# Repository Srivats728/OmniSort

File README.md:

# OmniSort

**The ultimate download and email manager.**

Have you ever just stared at your download folder or your email inbox in pure horror, looking at cluttered files and unread emails you didn't even know existed? Enter OmniSort, an all-in-one physical tool to quickly and easily sort your email inbox or download folder with absolute ease. Featuring an OLED display, 16 customizable switches, and a glorious rotary knob, tactility and ease of use you get with this product is unmatched. Follow along my journey of building this and bringing it to life! Thanks for reading.

*Built by Srivats Viswanathan*

---

## Build Log
*(CAD renders, schematics, and PCB layouts will be here once they are finished).*

## Hardware
* **Microcontroller:** Seeed XIAO RP2040 
* **Inputs:** 16x MX-Style Switches & 1x EC11 Rotary Encoder
* **Display:** 0.91-inch OLED 
* **Lighting:** 16x 1N4148 Diodes (for 4x4 matrix) & 16x SK6812 MINI-E RGB LEDs
* **Case:** 3D printed enclosure secured with M3 screws and heatset inserts

## How It Works
1. **Board:** Will use KMK to handle switch matrix, track dial, and update OLED screen. 
2. **Host:** A background Python script on PC will watch local folders and talking to email servers to route data whenever a switch is hit.

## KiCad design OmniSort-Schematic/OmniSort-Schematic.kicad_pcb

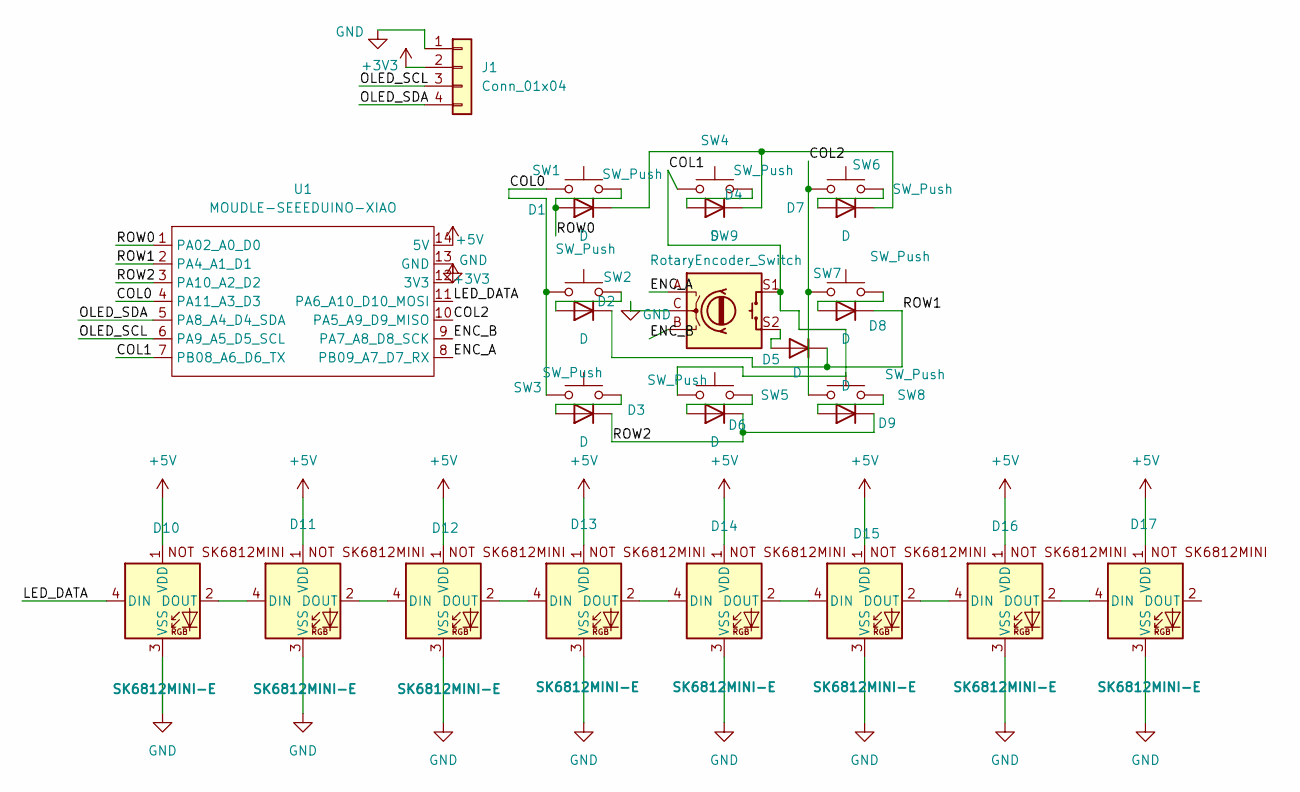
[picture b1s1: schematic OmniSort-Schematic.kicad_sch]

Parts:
D1, D2, D3, D4, D5, D6, D7, D8, D9: D; D_DO-35_SOD27_P7.62mm_Horizontal
D10, D11, D12, D13, D14, D15, D16, D17: SK6812MINI-E; SK6812MINI-E_fixed
J1: Conn_01x04; PinHeader_1x04_P2.54mm_Vertical
SW1, SW2, SW3, SW4, SW5, SW6, SW7, SW8: SW_Push; SW_Cherry_MX_1.00u_PCB
SW9: RotaryEncoder_Switch; RotaryEncoder_Alps_EC11E-Switch_Vertical_H20mm_MountingHoles
U1: MOUDLE-SEEEDUINO-XIAO; XIAO-Generic-Hybrid-14P-2.54-21X17.8MM

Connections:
+3V3: J1.2, U1.12 (3V3)
+5V: D10.1 (VDD), D11.1 (VDD), D12.1 (VDD), D13.1 (VDD), D14.1 (VDD), D15.1 (VDD), D16.1 (VDD), D17.1 (VDD), U1.14 (5V)
/COL0: SW1.1, SW2.1, SW3.1, U1.4 (PA11_A3_D3)
/COL1: SW4.1, SW5.1, SW9.S1, U1.7 (PB08_A6_D6_TX)
/COL2: SW6.1, SW7.1, SW8.1, U1.10 (PA5_A9_D9_MISO)
/ENC_A: SW9.A, U1.8 (PB09_A7_D7_RX)
/ENC_B: SW9.B, U1.9 (PA7_A8_D8_SCK)
/LED_DATA: D10.4 (DIN), U1.11 (PA6_A10_D10_MOSI)
/OLED_SCL: J1.3, U1.6 (PA9_A5_D5_SCL)
/OLED_SDA: J1.4, U1.5 (PA8_A4_D4_SDA)
/ROW0: D1.2 (A), SW1.2, U1.1 (PA02_A0_D0)
/ROW1: D2.1 (K), D5.1 (K), D8.1 (K), U1.2 (PA4_A1_D1)
/ROW2: D3.1 (K), D6.1 (K), D9.1 (K), U1.3 (PA10_A2_D2)
GND: D10.3 (VSS), D11.3 (VSS), D12.3 (VSS), D13.3 (VSS), D14.3 (VSS), D15.3 (VSS), D16.3 (VSS), D17.3 (VSS), J1.1, SW9.C, U1.13 (GND)
unnamed: D1.1 (K), D4.1 (K), D7.1 (K)
unnamed: D2.2 (A), SW2.2
unnamed: D3.2 (A), SW3.2
unnamed: D4.2 (A), SW4.2
unnamed: D5.2 (A), SW9.S2
unnamed: D6.2 (A), SW5.2
unnamed: D7.2 (A), SW6.2
unnamed: D8.2 (A), SW7.2
unnamed: D9.2 (A), SW8.2
unnamed: D10.2 (DOUT), D11.4 (DIN)
unnamed: D11.2 (DOUT), D12.4 (DIN)
unnamed: D12.2 (DOUT), D13.4 (DIN)
unnamed: D13.2 (DOUT), D14.4 (DIN)
unnamed: D14.2 (DOUT), D15.4 (DIN)
unnamed: D15.2 (DOUT), D16.4 (DIN)
unnamed: D16.2 (DOUT), D17.4 (DIN)

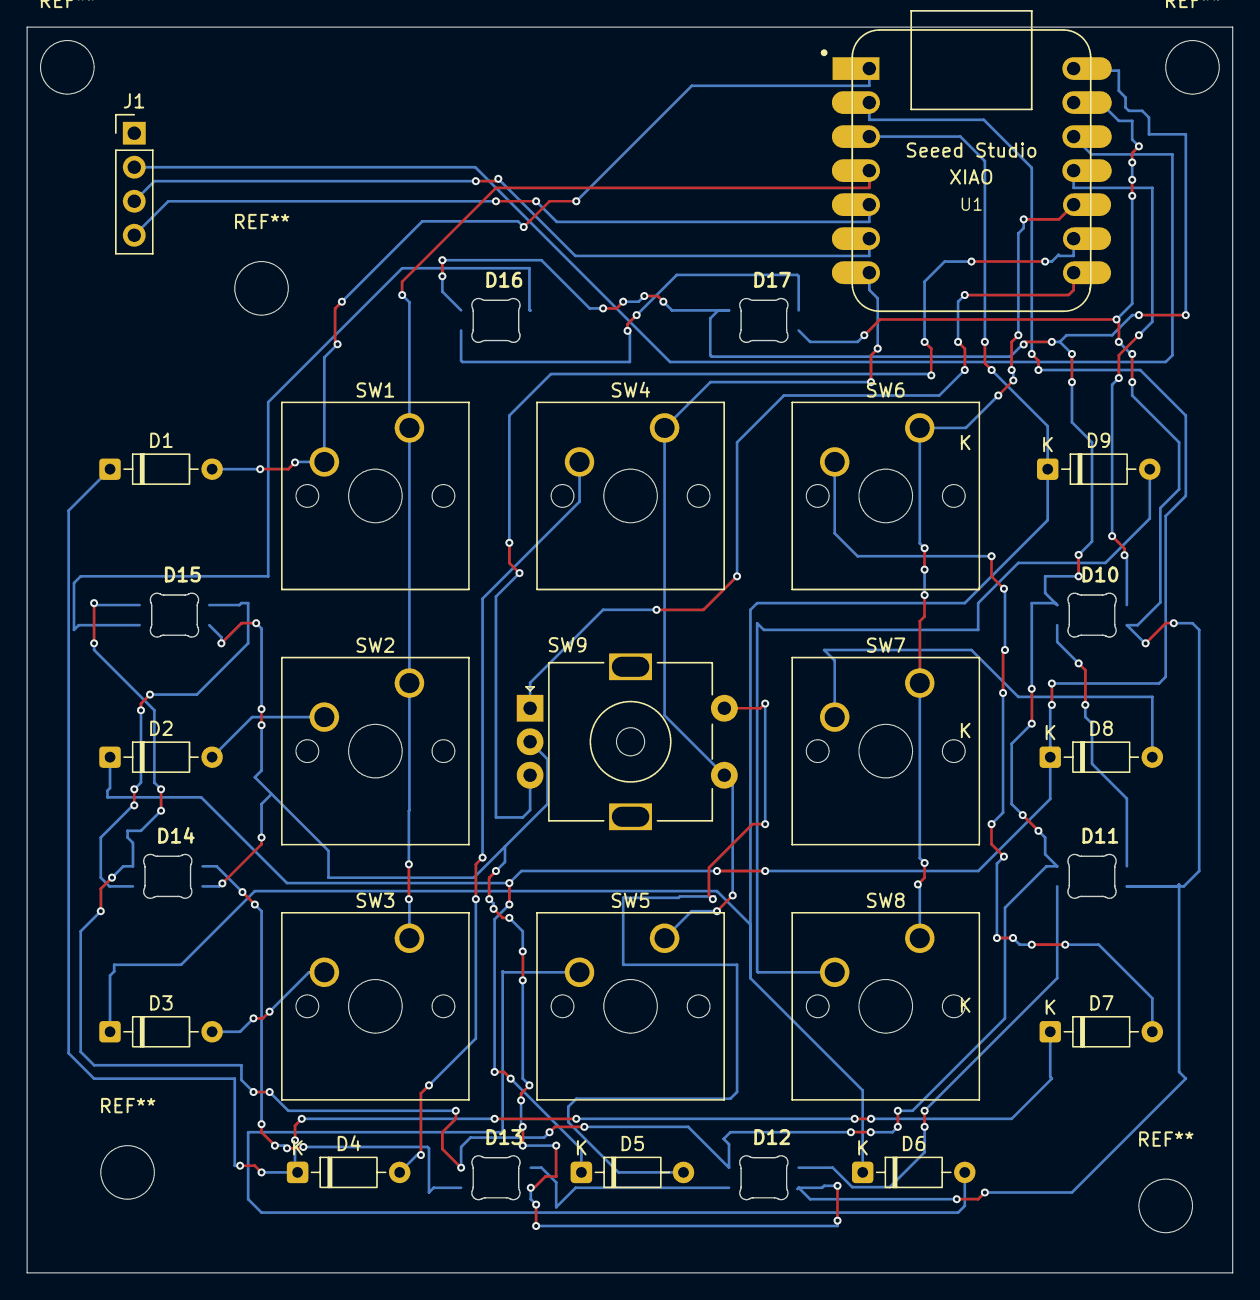
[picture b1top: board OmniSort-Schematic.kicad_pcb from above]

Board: 2 copper layers, 90.0 x 93.0 mm, 28 parts (0 on the bottom side), 30 nets.

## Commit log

2026-06-10 Added README.md
2026-06-10 Edit README.md
2026-06-12 Uploaded All Files
2026-06-13 Upload Partially Completed 3D Case models
2026-06-16 Schematic & PCB update
2026-06-18 Demo Prototype
2026-06-18 Add GitHub Actions workflow for static content deployment
    This workflow automates the deployment of static content to GitHub Pages upon pushes to the main branch or manual triggers.
2026-06-18 Refactor kicanvas-embed in index.html
    Updated kicanvas-embed structure and comments for clarity.
2026-06-18 Change kicanvas source to direct GitHub URL
    Updated kicanvas-embed source to use a direct URL for GitHub Pages compatibility.
2026-06-18 Change title and improve HTML layout
    Updated the title and modified the layout structure for better responsiveness.
2026-06-18 Add interactive instruction banner and copy button
2026-06-18 Final
2026-06-18 Update instruction text for PCB link
2026-06-19 PCB refinement
    Adjusted mounting hole sizes and trace routing around the holes
2026-06-19 More PCB refinement
2026-06-29 Create BOM.csv with project components
    Added a Bill of Materials (BOM) listing components for the project.
2026-06-29 Add KMK firmware main.py
2026-06-29 Update README to remove CircuitPython reference
